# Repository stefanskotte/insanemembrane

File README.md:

# insanemembrane

Replacement keyboard membranes for the **Commodore Amiga 1200, 500 and 600**, made as 2-layer polyimide flex PCBs
to be ordered from JLCPCB.

The originals are Mitsumi carbon-and-silver-ink membranes, and after 30+ years they crack and their traces break.
Each replacement is a **1:1 copy of the original**:
- the outline, holes, key pads and contacts are measured from 600 dpi scans of a real membrane;
- the matrix wiring is traced from the original's own silver traces and printed crossover bridges;
- the traces become gold-plated copper, with every trace and bridge at exactly 0°, 45° or 90°.

| | A1200 | A500 | A600 (green) |
|---|---|---|---|
| Original | Mitsumi 56C774A | Mitsumi A-500(E) 56 A619B | Mitsumi A300-B 30M 56C471B |
| Keys | 96 + Caps Lock LED | 96 + Caps Lock LED | 78 + Caps Lock LED |
| Connector | 31-pin tail, 1.25 mm | 31-finger tab, 1.25 mm | 30-pin tail, 1.25 mm |
| Board size | 237.0 × 440.0 mm | 134.5 × 441.1 mm | 249.8 × 316.9 mm |
| Status | rev A, **built, tested, fully working** | rev A, fit check passed | rev A, fit check passed |
| Folder | [`a1200/`](a1200/) | [`a500/`](a500/) | [`a600/`](a600/) |

**Planned:** the **blue A600 membrane**, the other A600 version, will follow once an original is available to scan.

---

## Amiga 1200 — Mitsumi 56C774A

<table><tr>
<td width="38%"></td>
<td><br><br>
</td>
</tr></table>

**Tested:** a rev A board from JLCPCB has been fitted to an A1200, and every key and the Caps Lock LED work.

The 31-pin tail plugs into CN13 on the A1200 motherboard. It is 10 mm shorter than the original, because the original
has spare length and bows when plugged in. A 0.10 mm PI stiffener behind the contacts brings them to 0.21 mm total, like
the original. The tail traces enter the contacts by a hand-routed method: each trace's 45° diagonal runs on to its
contact's height, then one straight line goes in.

## Amiga 500 — Mitsumi A-500(E) 56 A619B

<table><tr>
<td width="30%"></td>
<td><br><br>
</td>
</tr></table>

The A500 has no tail. Its 31 gold fingers sit on a short tab at the step in the outline and plug into the FFC connector
on the keyboard's controller board. A PI stiffener behind the fingers (7.86 mm, as on the original) brings them to about
0.40 mm. The outer corners are rounded to R 1.2 mm to match the original.

## Amiga 600 (green) — Mitsumi A300-B 30M 56C471B

<table><tr>
<td width="45%"></td>
<td><br><br>
</td>
</tr></table>

The original's tail is 180 mm long. Here it is shortened to 131.7 mm so the board stays inside JLC's 250 mm flex limit.
A 100 mm PI stiffener sits behind the 30 contacts. The original's notched corners and half-round edge notches are
copied from the scan.

---

## Ordering

Each membrane's `fab/` folder is a ready JLCPCB flex order:
- the Gerber + drill zip,
- `JLC-ORDER.md`, with the order-form settings and a remark short enough for JLC's notes field,
- a **1:1 fit-check PDF**: print it at 100 % and lay your original membrane on top to check the outline, holes and pads.

[`a1200/fab/ORDER-SETTINGS.md`](a1200/fab/ORDER-SETTINGS.md) compares the settings for all three side by side. The same
file is also in `a500/fab/` and `a600/fab/`.

In short, all three are:
- 2-layer flex, 0.11 mm,
- 0.5 oz copper,
- ENIG 2 µ",
- PI coverlay,
- with a PI stiffener on the bottom behind the contacts.

## How the boards are made

1. **Scan.** Each side of the membrane is scanned at 600 dpi on A4, in two halves, with printed rulers in view. The halves
   are lined up on the through-holes (to within ~0.04 mm) and stitched. The back side is mirrored onto the front.
2. **Measure.** Outline, holes, carbon key pads, the LED pads and the contacts are taken from the stitched scans. The
   skew and the scanner's Y scale are corrected.
3. **Trace the netlist.** The silver traces from the back scan are joined by the printed crossover bridges and by the
   carbon pads. Every key must end up on exactly two different connector pins, with no shorts. The A1200 is also checked
   against the skielek/A1200KB matrix.
4. **Route.** The silver traces become top copper and the bridges become bottom copper with tented vias. Every piece is
   then refitted to 0°/45°/90°, keeping ≥ 0.25 mm clearance and moving no more than 0.45 mm from the original.
5. **Build and check.** KiCad builds the board and runs DRC (all three: 0 violations, 0 unconnected). The script then
   exports the Gerbers, the drill files and the fit-check PDF.

## Repository layout

```
a1200/  a500/  a600/        one folder per membrane
  docs/                     design spec (with "as built"), working notes, stitched scans
  docs/scan-data/           measurements, netlist, routing, board geometry (JSON)
  kicad/                    KiCad 10 project
  fab/                      JLC order package + fit-check PDF + renders
tools/a1200|a500|a600/      per-model steps (make.sh, scan registration, geometry, replica routing)
tools/build/                shared stages: pads, heal, octi (0/45/90), tidy, build_board, check_print
tools/scan/                 generic scan helpers (holes, features, pad shape)
docs/                       project-wide: backlog, README images
```

The raw TIFF scans (≈100 MB each) are not in the repository.

## Rebuilding

You need KiCad 10 and a Python 3 venv in `.venv` with `numpy opencv-contrib-python-headless scipy shapely pillow`.
With the raw scans in the project root, rebuild a membrane with its own script:

```sh
tools/a1200/make.sh
tools/a500/make.sh
tools/a600/make.sh
```

Each script runs the whole chain from the scans through to the fab package.

## Licence

This project is licensed under [CC BY-NC-SA 4.0](LICENSE): you may build it for yourself, share it and adapt it with
credit, but not for commercial use, and adaptations must use the same licence. The A1200 key-matrix data comes from
[skielek/A1200KB](https://github.com/skielek/A1200KB) under the MIT licence; see [NOTICE](NOTICE).

**Not to be manufactured or sold by AmigaKit or RetroPassion**, in any form, including anything made from or derived
from this design.

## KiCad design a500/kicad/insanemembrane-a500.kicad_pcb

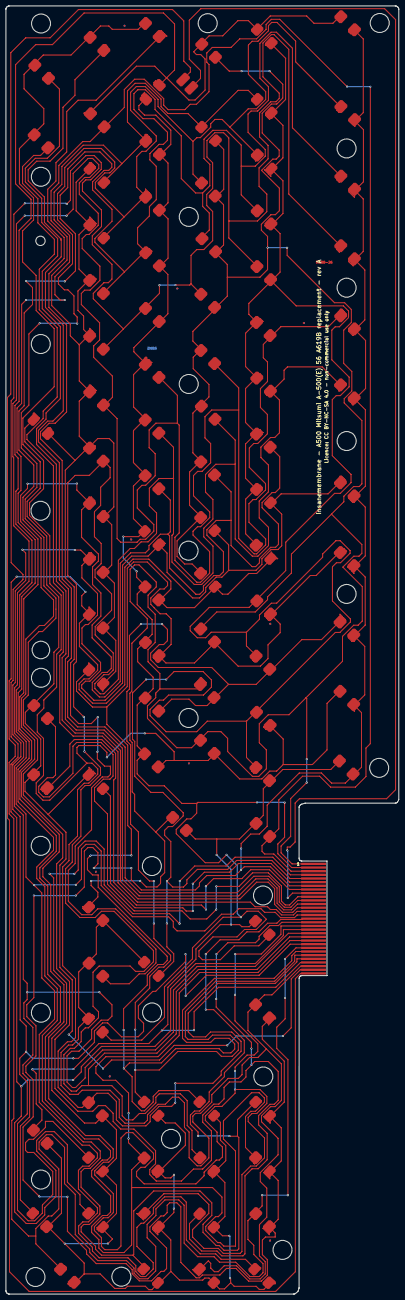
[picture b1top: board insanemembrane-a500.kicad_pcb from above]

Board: 2 copper layers, 134.5 x 441.1 mm, 129 parts (0 on the bottom side), 31 nets.

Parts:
D1: CAPS_LED
H1, H2, H3, H4, H5, H6, H7, H8, H9, H10, H11, H12, H13, H14, H15, H16, H17, H18, H19, H20, H21, H22, H23, H24, H25, H26, H27, H28, H29, H30, H31: NPTH
J1: CN13_TAIL_31P_1.25
K1: K1
K2: K2
K3: K3
K4: K4
K5: K5
K6: K6
K7: K7
K8: K8
K9: K9
K10: K10
K11: K11
K12: K12
K13: K13
K14: K14
K15: K15
K16: K16
K17: K17
K18: K18
K19: K19
K20: K20
K21: K21
K22: K22
K23: K23
K24: K24
K25: K25
K26: K26
K27: K27
K28: K28
K29: K29
K30: K30
K31: K31
K32: K32
K33: K33
K34: K34
K35: K35
K36: K36
K37: K37
K38: K38
K39: K39
K40: K40
K41: K41
K42: K42
K43: K43
K44: K44
K45: K45
K46: K46
K47: K47
K48: K48
K49: K49
K50: K50
K51: K51
K52: K52
K53: K53
K54: K54
K55: K55
K56: K56
K57: K57
K58: K58
K59: K59
K60: K60
K61: K61
K62: K62
K63: K63
K64: K64
K65: K65
K66: K66
K67: K67
K68: K68
K69: K69
K70: K70
K71: K71
K72: K72
K73: K73
K74: K74
K75: K75
K76: K76
K77: K77
K78: K78
K79: K79
K80: K80
K81: K81
K82: K82
K83: K83
K84: K84
K85: K85
K86: K86
K87: K87
K88: K88
K89: K89
K90: K90
K91: K91
K92: K92
K93: K93
K94: K94
K95: K95
K96: K96

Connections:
PIN01: J1.1, K5.2, K11.2, K17.2, K21.2, K26.2, K31.1, K36.1, K41.1, K46.1, K51.1, K56.1, K60.1, K65.1, K71.1, K73.1
PIN02: J1.2, K7.2, K13.2, K18.2, K23.2, K27.2, K32.1, K38.1, K42.1, K47.1, K52.1, K57.1, K62.1, K66.1, K74.2, K78.2
PIN03: J1.3, K10.2, K15.1, K20.1, K25.1, K30.1, K35.1, K37.2, K40.1, K45.2, K50.2, K54.2, K59.2, K72.2, K75.2
PIN04: J1.4, K79.2, K80.2, K81.2, K83.2, K84.2, K85.2, K86.2, K88.2, K89.2, K90.2, K91.2, K93.2, K94.2, K95.2, K96.2
PIN05: J1.5, K3.2, K8.2, K14.2, K19.2, K24.2, K29.1, K33.1, K39.1, K44.1, K48.1, K53.1, K58.1, K64.1, K68.1, K76.2
PIN06: J1.6, K70.2
PIN07: J1.7, K1.2, K9.2, K16.2, K22.2, K28.2, K34.2, K43.2, K49.2, K55.2, K61.2, K67.2, K77.2, K82.2, K87.2, K92.2
PIN08: J1.8, K69.2
PIN09: D1.2, J1.9
PIN10: J1.10, K63.2
PIN11: J1.11, K2.2
PIN12: J1.12, K4.2
PIN13: J1.13, K6.2
PIN14: J1.14, K12.2
PIN15: J1.15, K1.1, K3.1, K5.1, K7.1, K10.1, K96.1
PIN16: J1.16, K8.1, K11.1, K13.1, K15.2, K82.1, K94.1
PIN17: J1.17, K9.1, K14.1, K17.1, K18.1, K20.2, K91.1
PIN18: J1.18, K16.1, K19.1, K21.1, K23.1, K25.2, K90.1
PIN19: J1.19, K22.1, K24.1, K26.1, K27.1, K30.2, K89.1
PIN20: J1.20, K28.1, K29.2, K31.2, K32.2, K35.2, K88.1
PIN21: J1.21, K33.2, K34.1, K36.2, K38.2, K40.2, K86.1
PIN22: J1.22, K39.2, K41.2, K42.2, K45.1, K85.1, K87.1
PIN23: J1.23, K43.1, K44.2, K46.2, K47.2, K50.1, K84.1
PIN24: J1.24, K48.2, K51.2, K52.2, K54.1, K92.1, K93.1
PIN25: J1.25, K49.1, K53.2, K56.2, K57.2, K59.1, K81.1
PIN26: J1.26, K55.1, K58.2, K60.2, K62.2, K80.1
PIN27: J1.27, K37.1, K61.1, K64.2, K65.2, K66.2, K79.1
PIN28: J1.28, K67.1, K68.2, K71.2, K72.1, K74.1, K83.1
PIN29: J1.29, K73.2, K75.1, K76.1, K77.1, K78.1, K95.1
PIN30: J1.30, K2.1, K4.1, K6.1, K12.1, K63.1, K69.1, K70.1
PIN31: D1.1, J1.31

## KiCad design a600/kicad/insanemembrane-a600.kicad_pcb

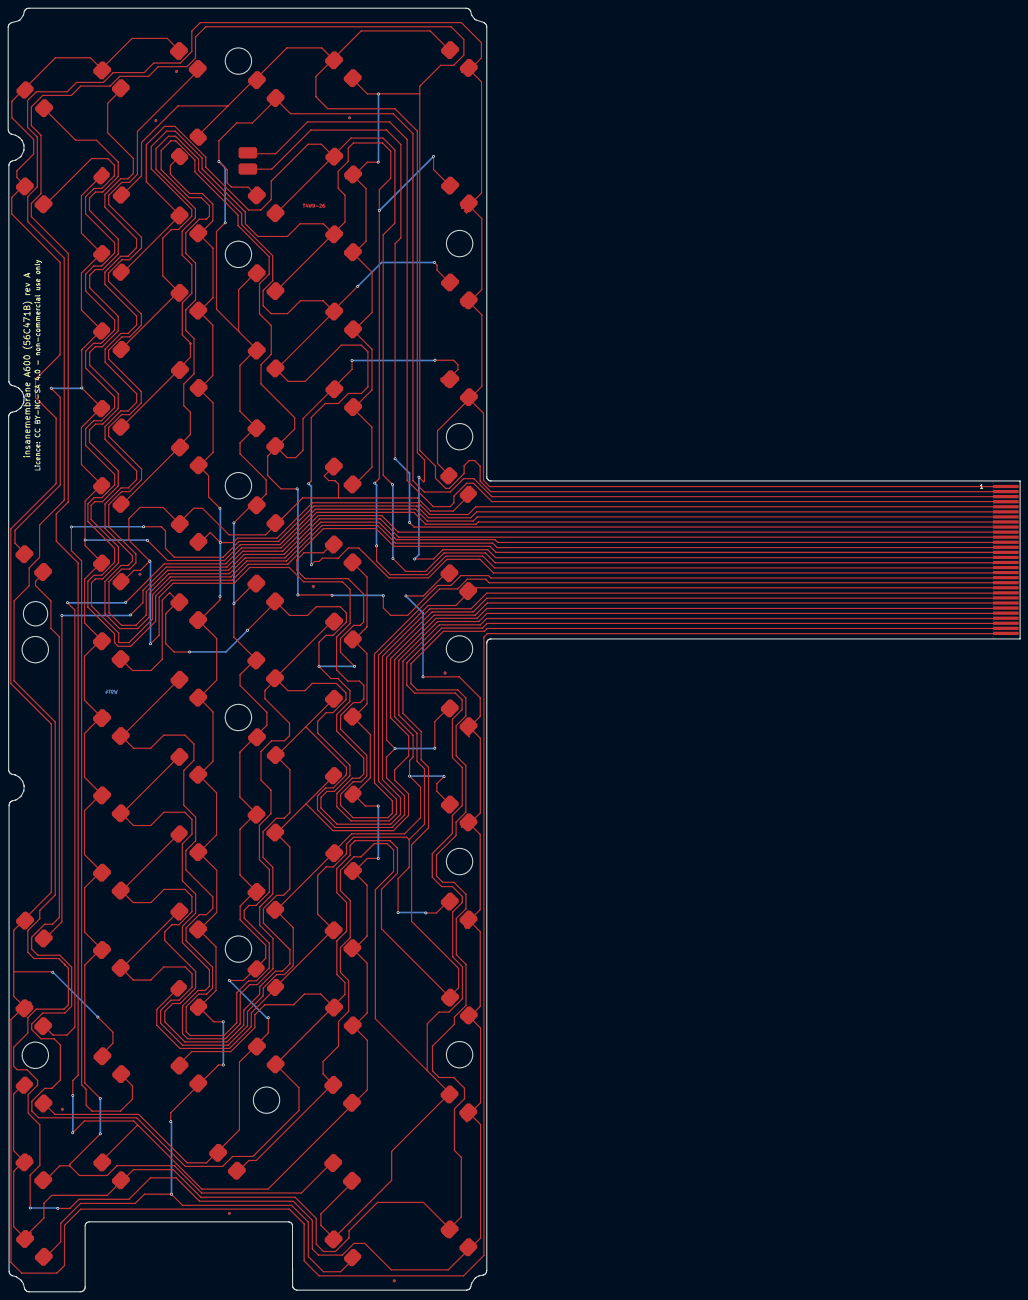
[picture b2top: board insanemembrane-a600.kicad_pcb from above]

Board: 2 copper layers, 249.8 x 316.9 mm, 96 parts (0 on the bottom side), 30 nets.

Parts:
D1: CAPS_LED
H1, H2, H3, H4, H5, H6, H7, H8, H9, H10, H11, H12, H13, H14, H15, H16: NPTH
J1: CN13_TAIL_31P_1.25
K1: K1
K2: K2
K3: K3
K4: K4
K5: K5
K6: K6
K7: K7
K8: K8
K9: K9
K10: K10
K11: K11
K12: K12
K13: K13
K14: K14
K15: K15
K16: K16
K17: K17
K18: K18
K19: K19
K20: K20
K21: K21
K22: K22
K23: K23
K24: K24
K25: K25
K26: K26
K27: K27
K28: K28
K29: K29
K30: K30
K31: K31
K32: K32
K33: K33
K34: K34
K35: K35
K36: K36
K37: K37
K38: K38
K39: K39
K40: K40
K41: K41
K42: K42
K43: K43
K44: K44
K45: K45
K46: K46
K47: K47
K48: K48
K49: K49
K50: K50
K51: K51
K52: K52
K53: K53
K54: K54
K55: K55
K56: K56
K57: K57
K58: K58
K59: K59
K60: K60
K61: K61
K62: K62
K63: K63
K64: K64
K65: K65
K66: K66
K67: K67
K68: K68
K69: K69
K70: K70
K71: K71
K72: K72
K73: K73
K74: K74
K75: K75
K76: K76
K77: K77
K78: K78

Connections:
PIN01: J1.1, K1.2, K10.2, K16.2, K22.2, K28.1, K35.1, K43.2, K49.2, K55.2, K62.2, K70.2, K75.2
PIN02: J1.2, K3.2, K8.2, K13.2, K18.2, K23.2, K27.2, K32.2, K38.2, K42.2, K47.2, K52.2, K58.2, K63.2, K68.2, K72.1
PIN03: J1.3, K5.2, K15.1, K20.1, K25.1, K30.1, K36.1, K40.1, K45.1, K50.1, K54.1, K60.1, K65.1, K69.2, K71.1, K78.1
PIN04: D1.1, J1.4
PIN05: J1.5, K7.2, K12.2, K17.2, K21.2, K26.2, K31.2, K37.2, K41.2, K46.2, K51.2, K56.2, K61.2, K67.2, K76.2, K77.2
PIN06: J1.6, K66.2
PIN07: J1.7, K9.1, K14.1, K19.1, K24.1, K29.1, K33.1, K34.1, K39.1, K44.1, K48.1, K53.1, K59.1, K73.1, K74.2
PIN08: J1.8, K64.2
PIN09: D1.2, J1.9
PIN10: J1.10, K57.2
PIN11: J1.11, K2.2
PIN12: J1.12, K4.2
PIN13: J1.13, K6.2
PIN14: J1.14, K11.2
PIN15: J1.15, K1.1, K3.1, K5.1, K7.1, K9.2
PIN16: J1.16, K8.1, K12.1, K14.2, K78.2
PIN17: J1.17, K10.1, K13.1, K15.2, K17.1, K19.2
PIN18: J1.18, K16.1, K18.1, K20.2, K21.1, K24.2
PIN19: J1.19, K22.1, K23.1, K25.2, K26.1, K29.2
PIN20: J1.20, K27.1, K28.2, K30.2, K31.1, K34.2
PIN21: J1.21, K32.1, K35.2, K36.2, K37.1, K39.2
PIN22: J1.22, K38.1, K40.2, K41.1, K44.2
PIN23: J1.23, K42.1, K43.1, K45.2, K46.1, K48.2
PIN24: J1.24, K47.1, K50.2, K51.1, K53.2
PIN25: J1.25, K49.1, K52.1, K54.2, K56.1, K59.2
PIN26: J1.26, K55.1, K58.1, K60.2, K61.1
PIN27: J1.27, K33.2, K62.1, K63.1, K65.2, K67.1
PIN28: J1.28, K68.1, K70.1, K71.2, K73.2, K76.1
PIN29: J1.29, K69.1, K72.2, K74.1, K75.1, K77.1
PIN30: J1.30, K2.1, K4.1, K6.1, K11.1, K57.1, K64.1, K66.1

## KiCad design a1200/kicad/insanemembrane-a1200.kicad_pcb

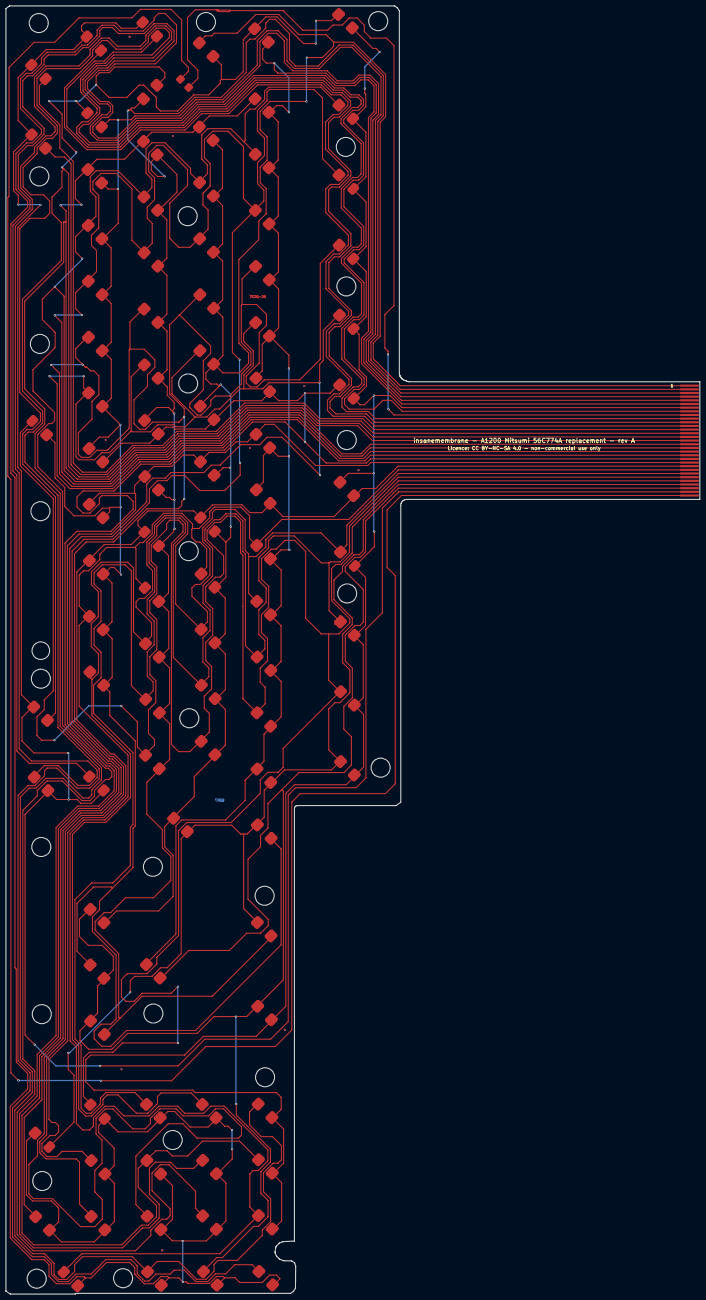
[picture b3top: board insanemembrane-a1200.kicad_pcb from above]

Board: 2 copper layers, 237.0 x 440.0 mm, 127 parts (0 on the bottom side), 31 nets.

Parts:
D1: CAPS_LED
H1, H2, H3, H4, H5, H6, H7, H8, H9, H10, H11, H12, H13, H14, H15, H16, H17, H18, H19, H20, H21, H22, H23, H24, H25, H26, H27, H28, H29: NPTH
J1: CN13_TAIL_31P_1.25
K1: ESC
K2: F1
K3: F2
K4: F3
K5: F4
K6: F5
K7: F6
K8: F7
K9: F8
K10: F9
K11: F10
K12: TILDE
K13: 1
K14: 2
K15: 3
K16: 4
K17: 5
K18: 6
K19: 7
K20: 8
K21: 9
K22: 0
K23: MINUS
K24: PLUS
K25: PIPE
K26: BS
K27: DEL
K28: HELP
K29: NUM_(
K30: NUM_)
K31: NUM_DIV
K32: NUM_MULT
K33: TAB
K34: Q
K35: W
K36: E
K37: R
K38: T
K39: Y
K40: U
K41: I
K42: O
K43: P
K44: L.CURLY
K45: R.CURLY
K46: RETURN
K47: NUM_7
K48: NUM_8
K49: NUM_9
K50: NUM_MINUS
K51: CTRL
K52: CAPSLOCK
K53: A
K54: S
K55: D
K56: F
K57: G
K58: H
K59: J
K60: K
K61: L
K62: COLON
K63: "
K64: R.BLANK
K65: UP
K66: NUM_4
K67: NUM_5
K68: NUM_6
K69: NUM_PLUS
K70: L.SHIFT
K71: L.BLANK
K72: Z
K73: X
K74: C
K75: V
K76: B
K77: N
K78: M
K79: R.CROC
K80: L.CROC
K81: QUESTION
K82: R.SHIFT
K83: LEFT
K84: DOWN
K85: RIGHT
K86: NUM_1
K87: NUM_2
K88: NUM_3
K89: NUM_ENTER
K90: L.ALT
K91: L.AMIGA
K92: SPACE
K93: R.AMIGA
K94: R.ALT
K95: NUM_0
K96: NUM_DECIMAL

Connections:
PIN01: J1.1, K33.1, K34.2, K35.2, K36.2, K37.2, K38.2, K39.1, K40.2, K41.2, K42.2, K43.2, K44.2, K45.2, K46.1, K83.2
PIN02: J1.2, K27.2, K52.2, K53.2, K54.2, K55.2, K56.2, K57.2, K58.1, K59.2, K60.2, K61.2, K62.2, K63.2, K64.2, K85.2
PIN03: J1.3, K26.2, K71.2, K72.2, K73.2, K74.2, K75.2, K76.2, K77.1, K78.2, K79.2, K80.2, K81.2, K84.1, K92.2
PIN04: J1.4, K32.2, K47.2, K48.2, K49.2, K50.2, K66.2, K67.2, K68.2, K69.2, K86.2, K87.2, K88.2, K89.2, K95.1, K96.2
PIN05: J1.5, K12.2, K13.2, K14.2, K15.2, K16.2, K17.2, K18.1, K19.2, K20.1, K21.2, K22.2, K23.2, K24.2, K25.1, K65.1
PIN06: J1.6, K82.1
PIN07: J1.7, K1.2, K2.2, K3.2, K4.2, K5.2, K6.2, K7.1, K8.2, K9.2, K10.2, K11.2, K28.2, K29.2, K30.2, K31.2
PIN08: J1.8, K94.1
PIN09: D1.2, J1.9
PIN10: J1.10, K93.2
PIN11: J1.11, K51.2
PIN12: J1.12, K70.2
PIN13: J1.13, K90.2
PIN14: J1.14, K91.2
PIN15: J1.15, K1.1, K12.1, K32.1, K33.2, K52.1, K71.1
PIN16: J1.16, K13.1, K29.1, K34.1, K53.1, K69.1, K72.1
PIN17: J1.17, K2.1, K14.1, K35.1, K49.1, K54.1, K73.1
PIN18: J1.18, K3.1, K15.1, K36.1, K55.1, K68.1, K74.1
PIN19: J1.19, K4.1, K16.1, K37.1, K56.1, K75.1, K88.1
PIN20: J1.20, K5.1, K17.1, K38.1, K57.1, K76.1, K96.1
PIN21: J1.21, K6.1, K18.2, K39.2, K48.1, K58.2, K77.2
PIN22: J1.22, K19.1, K30.1, K40.1, K59.1, K67.1, K78.1
PIN23: J1.23, K7.2, K20.2, K41.1, K60.1, K79.1, K87.1
PIN24: J1.24, K21.1, K31.1, K42.1, K61.1, K80.1, K89.1
PIN25: J1.25, K8.1, K22.1, K43.1, K47.1, K62.1, K81.1
PIN26: J1.26, K9.1, K23.1, K44.1, K63.1, K66.1
PIN27: J1.27, K10.1, K24.1, K45.1, K64.1, K86.1, K92.1
PIN28: J1.28, K11.1, K25.2, K26.1, K27.1, K46.2, K95.2
PIN29: J1.29, K28.1, K50.1, K65.2, K83.1, K84.2, K85.1
PIN30: J1.30, K51.1, K70.1, K82.2, K90.1, K91.1, K93.1, K94.2
PIN31: D1.1, J1.31

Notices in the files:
a1200/kicad/insanemembrane-a1200.kicad_pcb:
Licence: CC BY-NC-SA 4.0 - non-commercial use only
